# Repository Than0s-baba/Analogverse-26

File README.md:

# Analogverse-26
Project created for the Analogverse competetion held during Ingenium 2026, the annual techno cultural fest of IIT Indore. 

> The signals going around in the brain are quite small but still detectable through the thick skull and the skin. using general electrode inputs from the scalp, we can harness these signals, however, there exists a lot of noise and disturbances in the surroundings that hamper strongly with our readings, to clear those off and get our brain signal readings ready for processing, we have this project. :shipit:

## [The Problem Statement](https://docs.google.com/document/d/1ZouESIPnIgMfJ_Vj_Cs22WRU7gU9RRMwYfacLmLEe94/edit?tab=t.0): 
The Alpha-Wave Brain Computer Interface Front-End
The human brain emits distinct electrical patterns based on mental states. Alpha waves (8 Hz to 12 Hz) are prominent when a person is relaxed with their eyes closed. However, these signals at the scalp are incredibly weak (10 µV to 50 µV) and are easily drowned out by the 50 Hz powerline interference radiating from every wall outlet, as well as baseline wander from patient movement.
The Task: Design a single-channel, wearable Analog Front-End (AFE) that isolates and amplifies Alpha brainwaves from raw scalp electrode inputs. The output must be a clean, amplified signal ready to be fed into an standard 3.3V ADC (like an ESP32 or Arduino) for relaxation detection.
### Design Specifications:
- Total System Gain: 1000 to 5000 V/V (distributed appropriately to prevent rail saturation).
- Frequency Response (Bandpass): Strictly pass the 8 Hz to 12 Hz Alpha band. Frequencies below 0.5 Hz (DC offset/sweat artifacts) and above 30 Hz (muscle noise/EMG) must be heavily attenuated.
- Noise Rejection: Must include a dedicated stage to aggressively reject 50 Hz mains hum (minimum -40 dB attenuation at 50 Hz).
- Input Stage: Must handle differential inputs from three electrodes (Active, Reference, and Right Leg Drive/Ground) with a very high Common-Mode Rejection Ratio (CMRR).
- Power Supply: The circuit must operate on a single-supply (e.g., 3.3V or 5V) or dual-supply (+/- 5V or +/- 9V) derived from batteries, fitting a wearable form factor.
- PCB Constraints: Maximum board size of 100mm x 100mm.

### Deliverables:
**Phase1**: Simulation Instructions are attached, the Phase 1 Submission should involve output of the test mentioned , along with a report on the designed circuit justifying component choice.
**Phase2**: The Spice models will be tested with instantaneous testbenches on the location , the detailed presentation with simulation results and PCB layout to be presented in front of the Judges.

## [The Solution to Phase 1](Phase1/report.pdf)

## The Solution to Phase 2
too much efforts for completing and documenting the second part alone so just sharing the file. basically creating the whole schematic of the Phase 1 onto a PCB

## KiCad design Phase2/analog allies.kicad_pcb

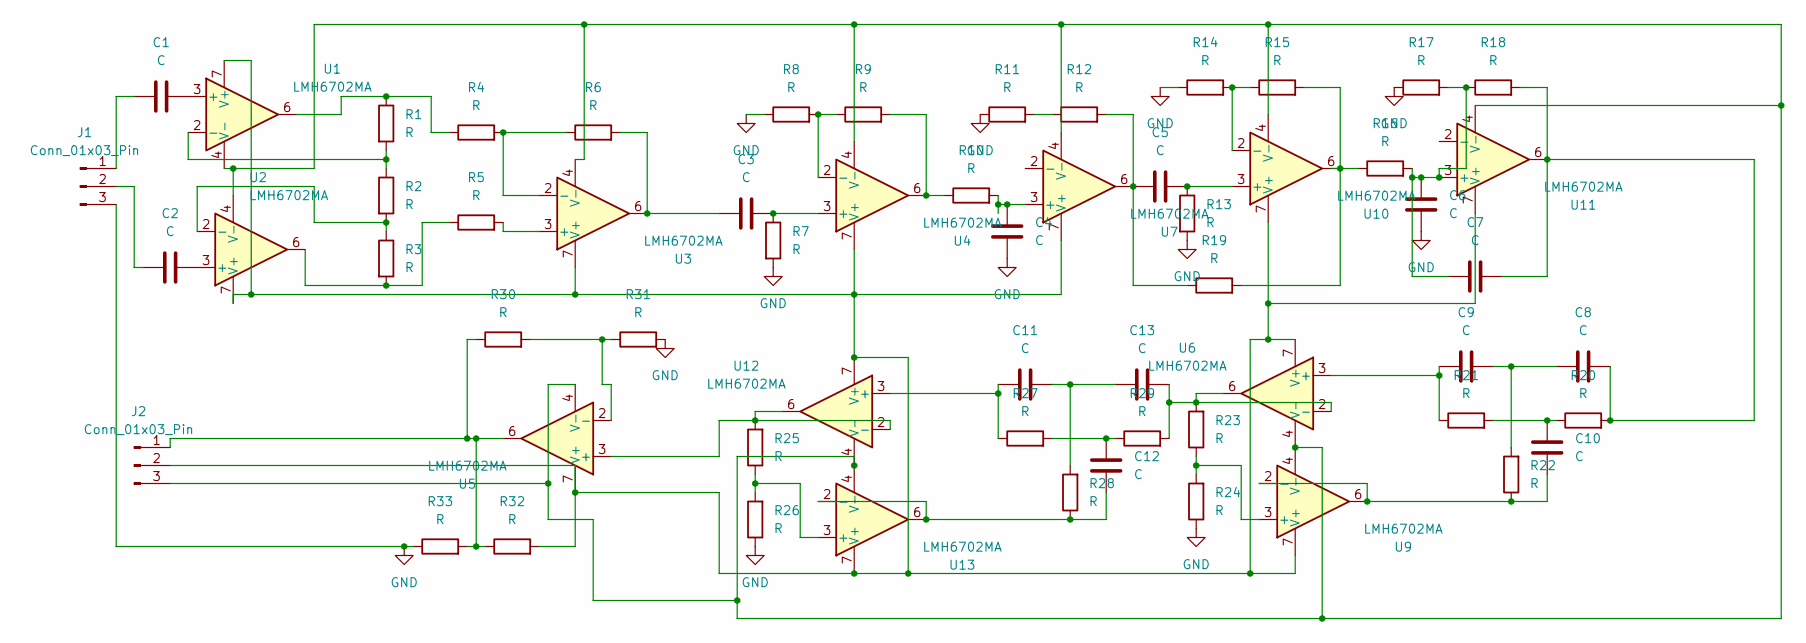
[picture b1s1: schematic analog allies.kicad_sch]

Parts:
C1, C2, C3, C4, C5, C6, C7, C8, C9, C10, C11, C12, C13: C; C_0805_2012Metric
J1, J2: Conn_01x03_Pin; PinHeader_1x03_P2.54mm_Vertical
R1, R2, R3, R4, R5, R6, R7, R8, R9, R10, R11, R12, R13, R14, R15, R16, R17, R18, R19, R20, R21, R22, R23, R24, R25, R26, R27, R28, R29, R30, R31, R32, R33: R; R_0805_2012Metric
U1, U2, U3, U4, U5, U6, U7, U9, U10, U11, U12, U13: LMH6702MA; SOIC-8_3.9x4.9mm_P1.27mm

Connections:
GND: C4.2, C6.2, J1.3, R7.2, R8.1, R11.1, R13.2, R14.1, R17.1, R24.1, R26.1, R31.2, R33.1
unnamed: C3.1, R6.2, U3.6
unnamed: C5.1, R12.2, R19.1, U7.6
unnamed: C7.2, C8.2, R18.2, R20.2, U11.6
unnamed: C8.1, C9.2, R22.2
unnamed: C10.2, R20.1, R21.2
unnamed: C11.2, C13.1, R28.2
unnamed: C12.2, R27.2, R29.1
unnamed: C1.1, J1.1
unnamed: C2.1, J1.2
unnamed: J2.1, R30.1, R32.1, R33.2, U5.6
unnamed: J2.2, R32.2, U1.7 (V+), U2.7 (V+), U3.7 (V+), U4.7 (V+), U5.7 (V+), U6.7 (V+), U7.7 (V+), U9.7 (V+), U10.7 (V+), U11.7 (V+), U12.7 (V+), U13.7 (V+)
unnamed: J2.3, U1.4 (V-), U2.4 (V-), U3.4 (V-), U4.4 (V-), U5.4 (V-), U6.4 (V-), U7.4 (V-), U9.4 (V-), U10.4 (V-), U11.4 (V-), U12.4 (V-), U13.4 (V-)
unnamed: R1.1, R4.1, U1.6
unnamed: R3.2, R5.1, U2.6
unnamed: R9.2, R10.1, U4.6
unnamed: R11.2, R12.1
unnamed: R15.2, R16.1, R19.2, U10.6
unnamed: C1.2, U1.3 (+)
unnamed: R1.2, R2.1, U1.2 (-)
unnamed: C2.2, U2.3 (+)
unnamed: R2.2, R3.1, U2.2 (-)
unnamed: R5.2, U3.3 (+)
unnamed: R4.2, R6.1, U3.2 (-)
unnamed: C3.2, R7.1, U4.3 (+)
unnamed: R8.2, R9.1, U4.2 (-)
unnamed: R30.2, R31.1, U5.2 (-)
unnamed: C9.1, R21.1, U6.3 (+)
unnamed: C13.2, R23.2, R29.2, U6.2 (-), U6.6
unnamed: C4.1, R10.2, U7.3 (+)
unnamed: R23.1, R24.2, U9.3 (+)
unnamed: C10.1, R22.1, U9.2 (-), U9.6
unnamed: C5.2, R13.1, U10.3 (+)
unnamed: R14.2, R15.1, U10.2 (-)
unnamed: C6.1, C7.1, R16.2, R17.2, R18.1, U11.3 (+)
unnamed: C11.1, R27.1, U12.3 (+)
unnamed: R25.2, U5.3 (+), U12.2 (-), U12.6
unnamed: R25.1, R26.2, U13.3 (+)
unnamed: C12.1, R28.1, U13.2 (-), U13.6

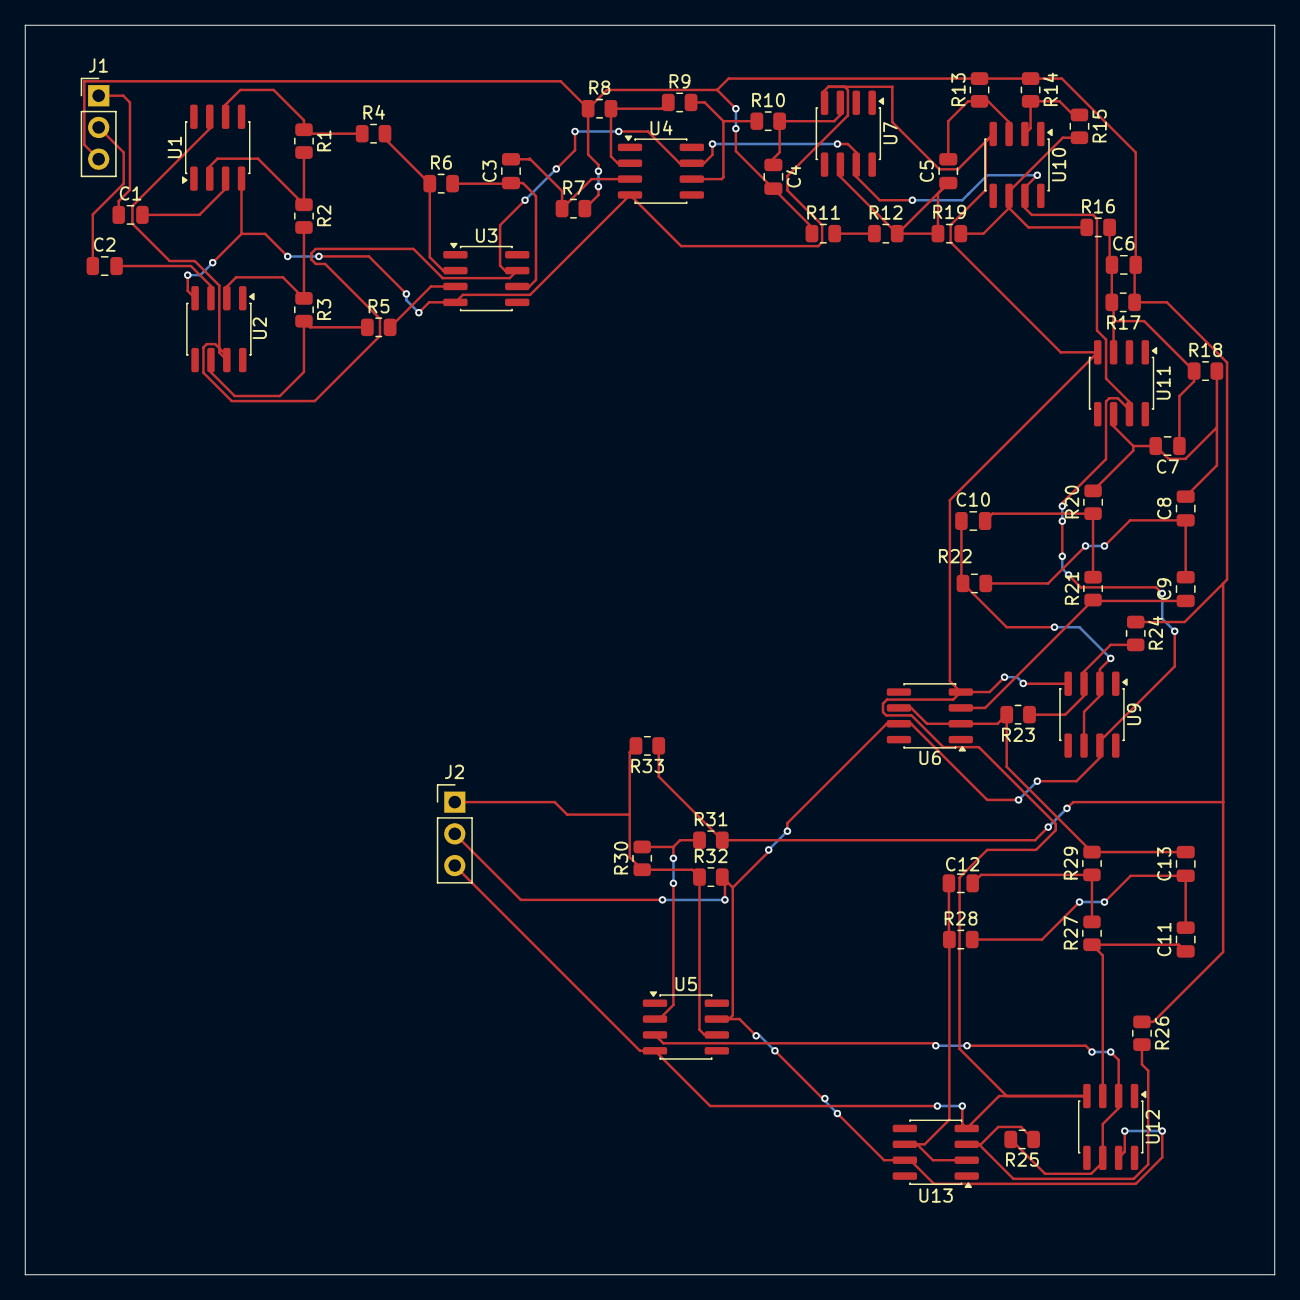
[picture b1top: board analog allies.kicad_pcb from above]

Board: 2 copper layers, 100.0 x 100.0 mm, 60 parts (0 on the bottom side), 39 nets.

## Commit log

2026-03-22 Update README with project details and specifications
    Expanded project details, problem statement, design specifications, and deliverables for the Analogverse-26 competition.
2026-03-22 Fix link case sensitivity for Phase 1 report
    Corrected the file name in the Phase 1 solution link from 'Report.pdf' to 'report.pdf'.
